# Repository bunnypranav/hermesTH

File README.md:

# Bunny's Hermes-TH

Hermes-TH is a small PCB that combines a temperature and humidity sensor, pressure sensor, and accelerometer, specifically the AHT20-F, AGR10, STK8328-C with a tiny OLED display, all controlled by a XIAO RP2040. The idea was to make a simple I2C-based board that reads environmental data that actually matters in my life, namely temperature, humidity, and pressure (unlike carbon monoxide for example), and displays it directly on a screen.

# Schematic
*Made in KiCad*

The XIAO RP2040 module handles everything. D4 and D5 are used for I2C (SCL and SDA), which are shared by the AHT20, OLED, and the accelerometer. The accelerometer is an analog device and read through the ADC pins of the RP2040, specifically A0. All other components are simply controlled through the I2C bus and everything is powered with 3.3V from the RP2040. The OLED is a 128x64 pixel display, which is more than enough for displaying all statistics.

# PCB
*Made in KiCad*

# BOM
* JLC PCBA: USD$37.5 (includes cost of some components)
* OLED: USD$1.9
* XIAO RP2040: USD$6.7
* Robu.in Shipping: USD$0.53
* **Total: USD$46.63**

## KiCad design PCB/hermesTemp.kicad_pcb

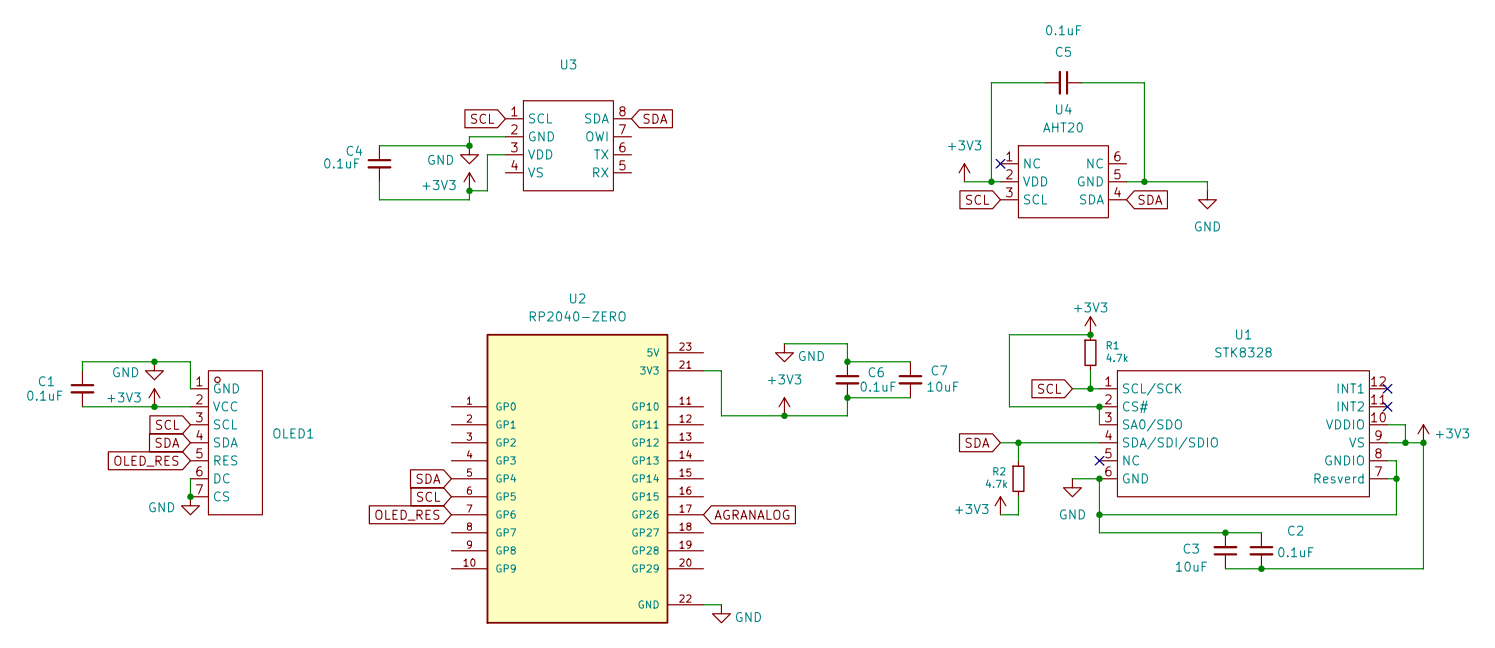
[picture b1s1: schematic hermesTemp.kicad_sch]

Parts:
C1, C2, C4, C5, C6: 0.1uF; C_0603_1608Metric
C3, C7: 10uF; C_0805_2012Metric
OLED1: OLED-TH_HS96L01W4S03; Manufacturer Part HS96L01W4S03; LCSC Part Name 0.96寸 白光 128x64像素分辨率
R1, R2: 4.7k; R_0603_1608Metric
U1: STK8328; VLGA-12_L2.0-W2.0-P0.50-BL; Manufacturer Part STK8328-C; LCSC Part Name 数字输出三轴MEMS加速度计
U2: RP2040-ZERO; MODULE_RP2040-ZERO; PARTREV NA
U3: LGA-8_L3.8-W3.6-P0.90-TL_WF183D; Manufacturer Part WF183DE 15BA L8N T&R; LCSC Part Name 数字压力传感器 量程：0-1500kpa 工作电压：2.4~5.5V 通信接口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
U4: AHT20; SENSOR-SMD-6_AHT20; Manufacturer Part AHT20-F; LCSC Part Name 温湿度传感器

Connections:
+3V3: C1.2, C2.2, C3.1, C4.2, C5.2, C6.2, C7.2, OLED1.2 (VCC), R1.1, R2.2, U1.2 (CS#), U1.3 (SA0/SDO), U1.9 (VS), U1.10 (VDDIO), U2.21 (3V3), U3.3 (VDD), U4.2 (VDD)
AGRANALOG: U2.17 (GP26)
GND: C1.1, C2.1, C3.2, C4.1, C5.1, C6.1, C7.1, OLED1.1 (GND), OLED1.6 (DC), OLED1.7 (CS), U1.6 (GND), U1.7 (Resverd), U1.8 (GNDIO), U2.22 (GND), U3.2 (GND), U4.5 (GND)
OLED_RES: OLED1.5 (RES), U2.7 (GP6)
SCL: OLED1.3 (SCL), R1.2, U1.1 (SCL/SCK), U2.6 (GP5), U3.1 (SCL), U4.3 (SCL)
SDA: OLED1.4 (SDA), R2.1, U1.4 (SDA/SDI/SDIO), U2.5 (GP4), U3.8 (SDA), U4.4 (SDA)

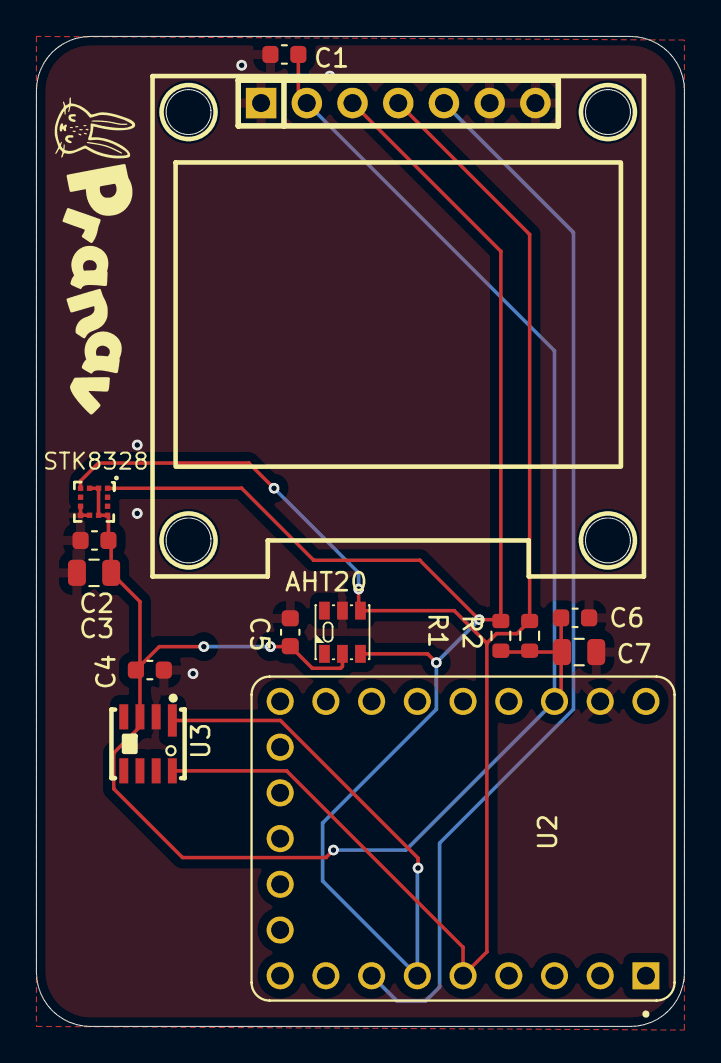
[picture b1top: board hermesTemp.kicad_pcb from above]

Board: 2 copper layers, 36.0 x 55.0 mm, 15 parts (1 on the bottom side), 5 nets.

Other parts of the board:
P2: LOGO

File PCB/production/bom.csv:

Designator,Footprint,Quantity,Value,LCSC Part #
"C1, C2, C4, C5, C6",0603,5,0.1uF,
"C3, C7",0805,2,10uF,
OLED1,OLED-TH_HS96L01W4S03,1,~,
"R1, R2",0603,2,4.7k,
U1,VLGA-12_L2.0-W2.0-P0.50-BL,1,STK8328,
U2,MODULE_RP2040-ZERO,1,RP2040-ZERO,
U3,LGA-8_L3.8-W3.6-P0.90-TL_WF183D,1,~,
U4,SENSOR-SMD-6_AHT20,1,AHT20,

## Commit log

2026-03-31 Update based on reviewer feedback.
    Switched to XIAO RP2040 (dropped STM32 + PCBA for MCU/OLED) to simplify design and reduce cost. Increased project complexity by adding STK8328 accelerometer and AGR10 pressure sensor alongside AHT20.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
2026-05-24 Build review update
2026-05-24 update build journal
